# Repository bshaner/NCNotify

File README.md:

# NCNotify-Core

*This project is a work-in-progress with a focus on learning, if you have suggestions or expertise to share, drop me a line!*

A nurse call BNC data logger, designed to work with any normally-open BNC nurse call system. I used publicly available datasheets and promo materials for the Airon pNeuton transport ventilator as a guide, but don't have one to test with. A test jig is coming (check the Documentation folder ... soon).

## Development
Permanent branches will be used for alternate layout ideas, pared-down implementations, or implementations with extra peripherals. Parens are used for branches I plan to start, but haven't jumped into:

* main: core development branch, on track for fab and assemble runs. Includes development headers, jumpers, no peripherals
* (bluetooth: bluetooth peripheral incl. Easy to integrate, but requires tighter power management (2 mcu). I'm interested in trying an all-nordic board down the road as a complete redesign, maybe with a wall-wart base station BT->Wi-Fi/Ethernet bridge)
	
## Principle of operation:
- Board runs on coin cell as fully pneumatic, mobile ventilator cannot supply power
- Nurse call connection (BNC-F) is normally-closed with an fairly high internal resistance (e.g. 51KOhm)
- MCU wakes regularly to poll the state of the nurse call relay, logging the state in flash with relative timestamps
- MCU offloads logging data to PC via USB to custom application, which translates events to absolute timestamps
	
## Other features/design goals:
- Battery status LED lights when Batt button is pressed, steady light for good battery health, flashing for low battery health
- Power optimization is a goal for firmware and design, aiming for months of operation on coin cell. Big concerns are 
	- cap leakage (decoupling caps likely to be removed/not populated), 
	- peak current consumption when polling/writing flash, 
	- deep sleep states vs timers needed for wakeup and timestamping events
	- current management for status LED over [~2.3?, 3.3]V given relatively large forward voltage drop
- Power from USB when available
	- Approach here was to try using a switch to detect when USB is plugged, because protection diodes and pmosfet would cause voltage drop and reduce battery life. But it is too big. Fun to try anyway!
	- Until a new solution comes up, jumpers will be used for USB vs BATT power mode, so testing doesn't use too many batteries
- Single-sided SMD assembly

## Known issues
	v1.0
		- SWD CLK and DIO are swapped

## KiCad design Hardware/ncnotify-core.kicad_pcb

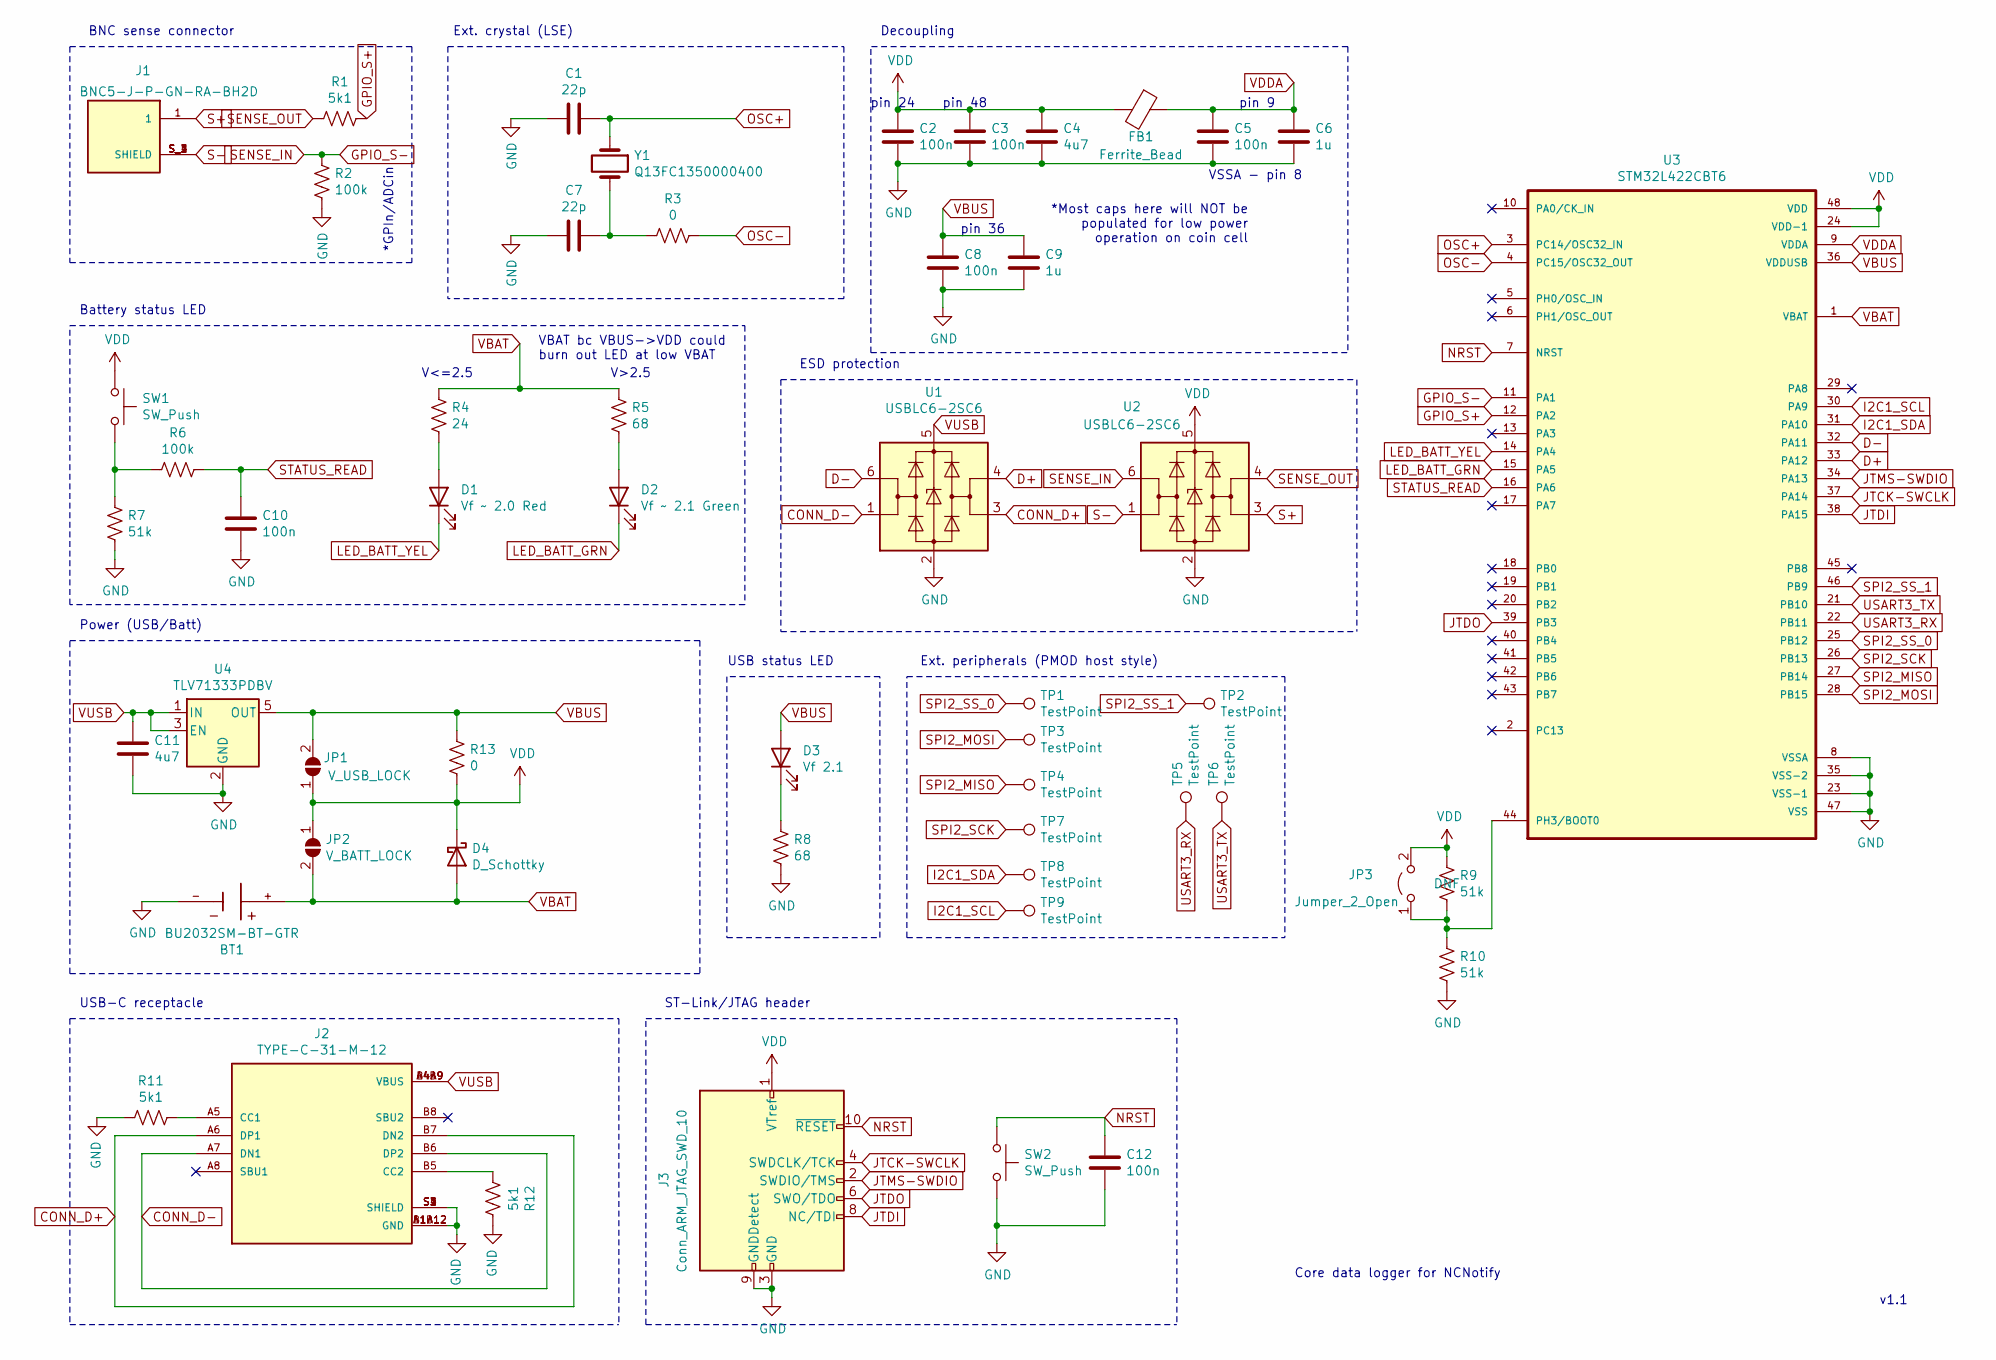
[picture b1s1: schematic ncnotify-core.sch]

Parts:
BT1: BU2032SM-BT-GTR; BAT_BU2032SM-BT-GTR; PARTREV F
C1, C7: 22p; C_0402_1005Metric; LCSC Part # C1555
C2, C3, C5, C8, C10, C12: 100n; C_0402_1005Metric; LCSC Part # C1525
C4, C11: 4u7; C_0603_1608Metric; LCSC Part # C19666
C6, C9: 1u; C_0402_1005Metric; LCSC Part # C52923
D1: Vf ~~ 2.0 Red; LED_0603_1608Metric; LCSC Part # C72038
D2: Vf ~~ 2.1 Green; LED_0603_1608Metric; LCSC Part # C72038
D3: Vf ~ 2.1; LED_0603_1608Metric; LCSC Part # C72038
D4: D_Schottky; D_SOD-323
FB1: Ferrite_Bead; L_0805_2012Metric; LCSC Part # C1015
J1: BNC5-J-P-GN-RA-BH2D; SAMTEC_BNC5-J-P-GN-RA-BH2D; PARTREV C
J2: TYPE-C-31-M-12; HRO_TYPE-C-31-M-12; PARTREV A; LCSC Part # C165948
J3: Conn_ARM_JTAG_SWD_10; PinHeader_2x05_P1.27mm_Vertical
JP1: V_USB_LOCK; SolderJumper-2_P1.3mm_Open_TrianglePad1.0x1.5mm
JP2: V_BATT_LOCK; SolderJumper-2_P1.3mm_Open_TrianglePad1.0x1.5mm
JP3: Jumper_2_Open; PinHeader_1x02_P1.27mm_Vertical
R1, R11, R12: 5k1; R_0402_1005Metric; LCSC Part # C25905
R2, R6: 100k; R_0402_1005Metric; LCSC Part # C25741
R3: 0; R_0402_1005Metric; LCSC Part # C17168
R4: 24; R_0603_1608Metric; LCSC Part # C22810
R5, R8: 68; R_0603_1608Metric; LCSC Part # C27592
R7, R9, R10: 51k; R_0402_1005Metric; LCSC Part # C25794
R13: 0; R_0402_1005Metric
SW1, SW2: SW_Push; TS-1187A; LCSC Part # C318884
TP1, TP2, TP3, TP4, TP5, TP6, TP7, TP8, TP9: TestPoint; TestPoint_Pad_D1.5mm
U1, U2: USBLC6-2SC6; SOT-23-6; LCSC Part # C7519
U3: STM32L422CBT6; QFP50P900X900X160-48N; LCSC Part # C94785
U4: TLV71333PDBV; SOT-23-5; LCSC Part # C90840
Y1: Q13FC1350000400; Crystal_SMD_3215-2Pin_3.2x1.5mm; LCSC Part # C32346

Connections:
CONN_D+: J2.A6 (DP1), J2.B7 (DN2), U1.3 (I/O2)
CONN_D-: J2.A7 (DN1), J2.B6 (DP2), U1.1 (I/O1)
D+: U1.4 (I/O2), U3.33 (PA12)
D-: U1.6 (I/O1), U3.32 (PA11)
GND: BT1.-, C1.2, C2.2, C3.2, C4.2, C5.2, C6.2, C7.2, C8.2, C9.2, C10.2, C11.2, C12.2, J2.A1B12 (GND), J2.B1A12 (GND), J2.S1 (SHIELD), J2.S2 (SHIELD), J2.S3 (SHIELD), J2.S4 (SHIELD), J3.3 (GND), J3.5 (GND), J3.9 (GNDDetect), R2.1, R7.2, R8.2, R10.2, R11.2, R12.1, SW2.2, U1.2 (GND), U2.2 (GND), U3.8 (VSSA), U3.23 (VSS-1), U3.35 (VSS-2), U3.47 (VSS), U4.2 (GND)
GPIO_S+: R1.1, U3.12 (PA2)
GPIO_S-: R2.2, U2.6 (I/O1), U3.11 (PA1)
I2C1_SCL: TP9.1, U3.30 (PA9)
I2C1_SDA: TP8.1, U3.31 (PA10)
JTCK-SWCLK: J3.4 (SWDCLK/TCK), U3.37 (PA14)
JTDI: J3.8 (NC/TDI), U3.38 (PA15)
JTDO: J3.6 (SWO/TDO), U3.39 (PB3)
JTMS-SWDIO: J3.2 (SWDIO/TMS), U3.34 (PA13)
LED_BATT_GRN: D2.1 (K), U3.15 (PA5)
LED_BATT_YEL: D1.1 (K), U3.14 (PA4)
NRST: C12.1, J3.10 (~RESET~), SW2.1, U3.7 (NRST)
unnamed: C7.1, R3.1, Y1.2
unnamed: D1.2 (A), R4.2
unnamed: D2.2 (A), R5.2
unnamed: D3.1 (K), R8.1
unnamed: J2.A5 (CC1), R11.1
unnamed: J2.B5 (CC2), R12.2
unnamed: JP3.1 (A), R9.2, R10.1, U3.44 (PH3/BOOT0)
unnamed: R6.2, R7.1, SW1.2
OSC+: C1.1, U3.3 (PC14/OSC32_IN), Y1.1
OSC-: R3.2, U3.4 (PC15/OSC32_OUT)
S+: J1.1, U2.3 (I/O2)
S-: J1.S_1 (SHIELD), J1.S_2 (SHIELD), J1.S_3 (SHIELD), J1.S_4 (SHIELD), U2.1 (I/O1)
SENSE_OUT: R1.2, U2.4 (I/O2)
SPI2_MISO: TP4.1, U3.27 (PB14)
SPI2_MOSI: TP3.1, U3.28 (PB15)
SPI2_SCK: TP7.1, U3.26 (PB13)
SPI2_SS_0: TP1.1, U3.25 (PB12)
SPI2_SS_1: TP2.1, U3.46 (PB9)
STATUS_READ: C10.1, R6.1, U3.16 (PA6)
USART3_RX: TP5.1, U3.22 (PB11)
USART3_TX: TP6.1, U3.21 (PB10)
VBAT: BT1.+, D4.2 (A), JP2.2 (B), R4.1, R5.1, U3.1 (VBAT)
VBUS: C8.1, C9.1, D3.2 (A), JP1.2 (B), R13.1, U3.36 (VDDUSB), U4.5 (OUT)
VDD: C2.1, C3.1, C4.1, D4.1 (K), FB1.2, J3.1 (VTref), JP1.1 (A), JP2.1 (A), JP3.2 (B), R9.1, R13.2, SW1.1, U2.5 (VBUS), U3.24 (VDD-1), U3.48 (VDD)
VDDA: C5.1, C6.1, FB1.1, U3.9 (VDDA)
VUSB: C11.1, J2.A4B9 (VBUS), J2.B4A9 (VBUS), U1.5 (VBUS), U4.1 (IN), U4.3 (EN)

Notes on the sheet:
Ext. crystal (LSE)
BNC sense connector
USB-C receptacle
Power (USB/Batt)
ST-Link/JTAG header
Battery status LED
Decoupling
*GPIn/ADCin
USB status LED
V<=2.5
V>2.5
VBAT bc VBUS->VDD could burn out LED at low VBAT
ESD protection
Ext. peripherals (PMOD host style)
VSSA - pin 8
pin 9
pin 36
pin 48
pin 24
*Most caps here will NOT be populated for low power operation on coin cell
Core data logger for NCNotify
v1.1

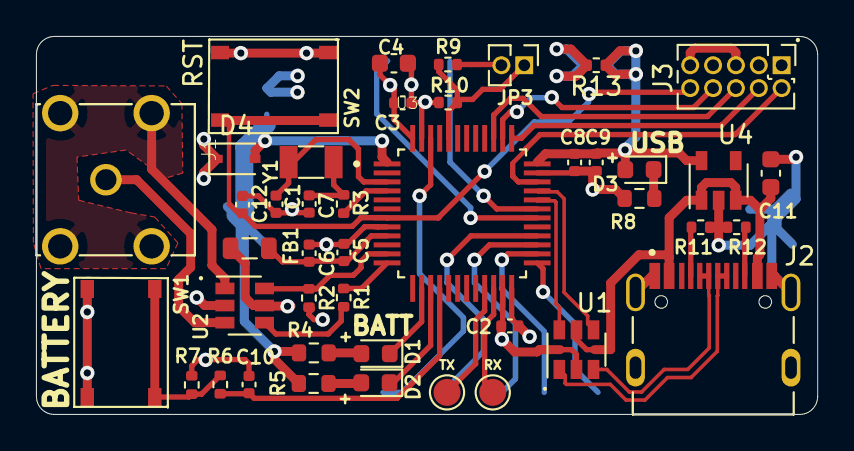
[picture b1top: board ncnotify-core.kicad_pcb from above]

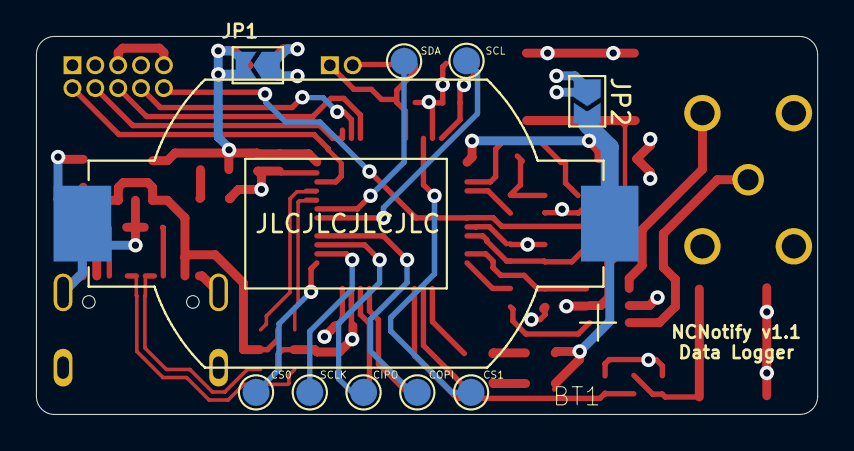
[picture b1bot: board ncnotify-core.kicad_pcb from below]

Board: 4 copper layers, 43.4 x 21.0 mm, 53 parts (10 on the bottom side), 42 nets.

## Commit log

2020-11-29 Schematic and rough placement
2020-11-29 Remove switches and expansion header
2020-11-30 Routing and replaced USB ESD chip
2020-11-30 lcsc part numbers for bom, cleanup before trying gerbers
2020-12-01 Cleanup silkscreen, add part numbers to sch bom
2020-12-01 bump to developing version v1.1
2020-12-02 Fix SWD CLK/DIO pin swap, add UART test points
2020-12-11 Board shrink; swap to RA BNC mount
2020-12-16 sizeup batt to 2032 for current limit; re-place to fit
2020-12-20 Resolve TH conflicts; add 3d models
2020-12-29 micro-usb connector
2021-01-08 Change batt status leds; add spi/i2c test points
2021-04-18 swap usb port and reroute
2021-05-04 add zener option for power flexibility
